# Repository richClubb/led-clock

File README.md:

# LED Clock

A desk or wall LED clock based on the LED rings 

* Neopixel ring 12 LED - https://www.adafruit.com/product/1643
* Neopixel ring 24 LED - https://www.adafruit.com/product/1586

## Objectives

* Easy for people to modify / use
* Use an RTC to keep time even when it's off
* Use NTP to update time
* Single code to handle all 3 clock variants
* Web page to set time
* Using serial to set config
  * Change strip that each time unit is displayed on
  * Change colour of each unit
* Self hosted network for setup
* Timer functionality
  * start, pause, reset
  * programmable / controllable from buttons on device
  * config from serial, stored in EEPROM
  * Config for: Colour, number of flashes when completed, time increment for buttons(seconds, minutes, number of minutes per press)
* Programmed in Rust
  * This is stage 2

The idea is that this is could be a product that I could sell, either as a finished clock or as a kit, but it's easy enough that it can be assembled by secondary school students.

## Demos

### Basic Functionality

[Basic time movement](./docs/images/second_minute_smooth_movement.mp4)

This video shows the movements of seconds, minutes and hours and how they blend together and move around the rings.

### Time Unit Config

[Time unit config](./docs/images/time_unit_change_colour.mp4)

This video shows the colour change config of the seconds unit. It can also be re-assigned to either of the two rings

### Timer functionality

[Timer Functionality](./docs/images/timer_function.mp4)

This video shows the timer working. The timer is for 10s and then flashes to show completion.

## Docs

* [Updates](./UPDATES.md) - Updates for the "12 Projects in 12 Months" Idea
* [Notes](./docs/NOTES.md) - General notes
* [Install](./docs/INSTALL.md) - Installing and programming

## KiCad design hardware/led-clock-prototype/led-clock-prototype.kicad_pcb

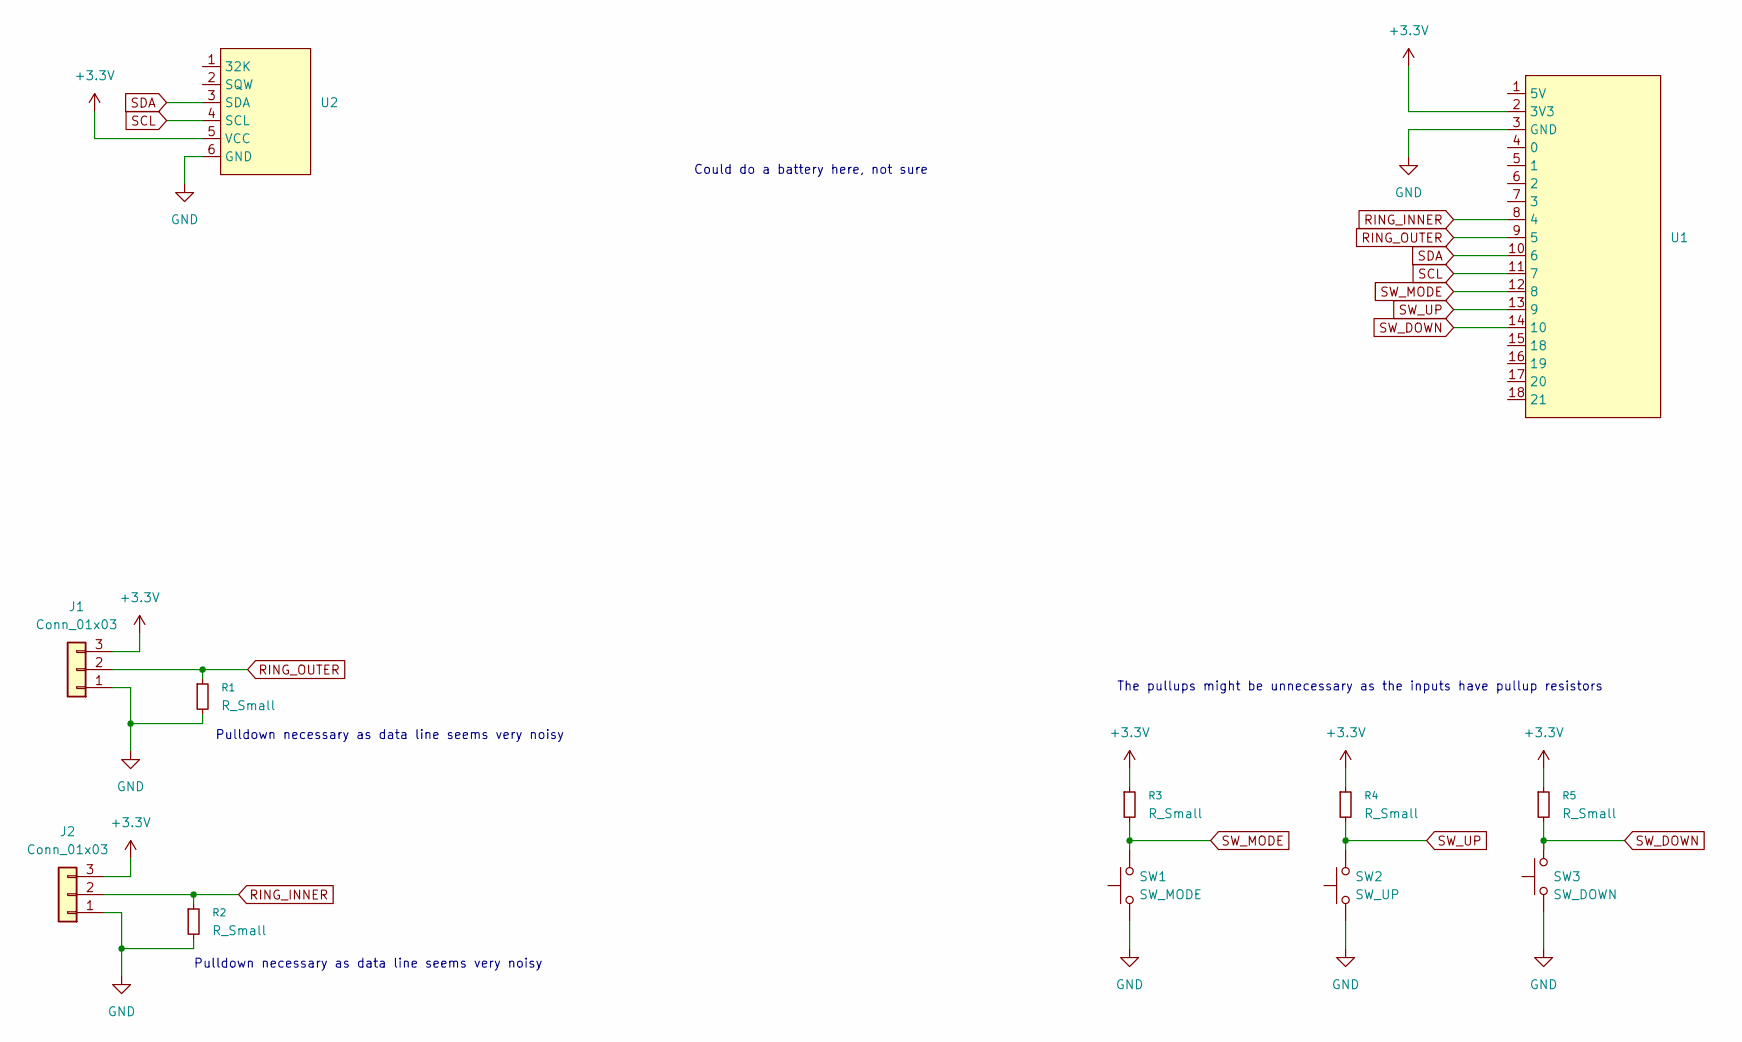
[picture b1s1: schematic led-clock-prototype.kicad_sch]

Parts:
J1, J2: Conn_01x03; PinHeader_1x03_P2.54mm_Vertical
R1, R2, R3, R4, R5: R_Small; R_1206_3216Metric_Pad1.30x1.75mm_HandSolder
SW1: SW_MODE; SW_PUSH_6mm
SW2: SW_UP; SW_PUSH_6mm
SW3: SW_DOWN; SW_PUSH_6mm
U1: Waveshare_ESP32_C3_Zero
U2: PinHeader_1x06_P2.54mm_Vertical

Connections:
+3.3V: J1.3, J2.3, R3.1, R4.1, R5.1, U1.2 (3V3), U2.5 (VCC)
GND: J1.1, J2.1, R1.2, R2.2, SW1.1, SW2.1, SW3.1, U1.3 (GND), U2.6 (GND)
RING_INNER: J2.2, R2.1, U1.8 (4)
RING_OUTER: J1.2, R1.1, U1.9 (5)
SCL: U1.11 (7), U2.4 (SCL)
SDA: U1.10 (6), U2.3 (SDA)
SW_DOWN: R5.2, SW3.2, U1.14 (10)
SW_MODE: R3.2, SW1.2, U1.12 (8)
SW_UP: R4.2, SW2.2, U1.13 (9)

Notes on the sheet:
Pulldown necessary as data line seems very noisy
Could do a battery here, not sure
The pullups might be unnecessary as the inputs have pullup resistors

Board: 2 copper layers, 12 parts (0 on the bottom side), 9 nets, no tracks yet.

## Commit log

2025-08-11 Moved into own repo from misc-projects
2025-08-11 small change to update
2025-08-12 random update
2025-08-13 docs changes and small refactor of serial interpreter
2025-08-13 added install doc
2025-08-13 Minor refactor of the led strip class
2025-08-13 corrected issue with millis offset (untested)
2025-08-14 Added in the eeprom / preferences logic for storing the config
2025-08-14 Working time unit config
2025-08-14 small fixes
2025-08-20 Added devcontainer and basic sketch for rust application
2025-09-01 Added in test for hello_world serial for rust
